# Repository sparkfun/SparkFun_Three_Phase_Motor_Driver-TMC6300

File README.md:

SparkFun 3-Phase BLDC Motor Driver - TMC6300
========================================

[*SparkFun 3-Phase BLDC Motor Driver - TMC6300 (ROB-21867)*](https://www.sparkfun.com/products/21867)

The TMC6300 from [ADI + Trinamic](https://www.trinamic.com/) is a powerful and easy to use three phase motor driver that was designed to control our [Brushless Gimbal Motor](https://www.sparkfun.com/products/20441). However, it can be used to control any 3-phase [BLDC](https://en.wikipedia.org/wiki/Brushless_DC_electric_motor "brushless DC") or [PMSM](https://en.wikipedia.org/wiki/Synchronous_motor#Permanent-magnet "permanent magnet synchronous motor") motor with up to 2A (1.4A<sub>RMS</sub>) of total drive current. Separate high-side and low-side control of the three half-bridges allows for incredible control of each phase of the [motor commutation](https://fab.cba.mit.edu/classes/865.21/topics/power_electronics/commutation/#bldc-commutation). The driver also provides temperature and short circuit protections; and a diagnostic output to indicate system faults. With a 1.8V regulated power output and an operating voltage down to 2V, the TMC6300 is suitable for low-power microcontroller and battery powered designs (min. 2 AA/NiMh cells, or 1-2 Li-Ion cells).

Our board layout has been designed with the LEDs and labels facing up, IC down. This allows the thermal pad on the board to be access if cooling is required. Additionally, the breakout pins are specially aligned to fit perfectly onto a breadboard and hold the headers more perpendicular to facilitate assembly.

Controlling 3-phase motors is not trivial and this board requires 6 PWM signals to fully control one motor. We've found the [*Arduino Simple Field Oriented Control*](https://docs.simplefoc.com/) library to work well with the board; however, there are some hadware limitations such as [supported microconrollers for `6PWM Mode`](https://docs.simplefoc.com/microcontrollers#supported-microcontrollers). With additional considerations, for integrating [position sensors](https://docs.simplefoc.com/position_sensors) into the feedback control loop.

Repository Contents
-------------------

* **[/docs](/docs/)** - Online documentation files
    * [arduino_examples](/docs/arduino_examples/) - Example code
    * [board_files](/docs/board_files/) - Files for the product design
            * [Eagle design files](/docs/board_files/eagle_files.zip) (.zip)
            * [Schematic](/docs/board_files/schematic.pdf) (.pdf)
            * [Dimensions](/docs/board_files/dimensions.pdf) (.pdf)
    * [component_documentation](/docs/component_documentation/) - Datasheets for hardware components
    * [img/hookup_guide/](/docs/img/hookup_guide/) - Images for hookup guide documentation
* **[/Hardware](/Hardware/)** - Eagle design files (.brd, .sch)

Documentation
--------------
* **[Hookup Guide (mkdocs)](http://docs.sparkfun.com/SparkFun_Three_Phase_Motor_Driver-TMC6300/)** - Hookup guide for the TMC6300 Motor Driver hosted by GitHub pages.

*Need to download or print our hookup guide?*

* [Print *(Print to PDF)* from Single-Page View](http://docs.sparkfun.com/SparkFun_Three_Phase_Motor_Driver-TMC6300/single_page)
* [Download PDF](http://docs.sparkfun.com/SparkFun_Three_Phase_Motor_Driver-TMC6300/board_files/hookup_guide.pdf) *(Beta - Mostly works, but some attributes may be broken.)*

Product Variants
----------------
* [ROB-21867](https://www.sparkfun.com/products/21867)- v1.0, Initial Release

Version History
---------------
* [v01](https://github.com/sparkfun/SparkFun_Three_Phase_Motor_Driver-TMC6300/releases/tag/v10) - Initial Release

License Information
-------------------

This product is _**open source**_! 

Please review the LICENSE.md file for license information. 

If you have any questions or concerns about licensing, please contact technical support on our [SparkFun forums](https://forum.sparkfun.com/viewforum.php?f=152).

Distributed as-is; no warranty is given.

- Your friends at SparkFun.

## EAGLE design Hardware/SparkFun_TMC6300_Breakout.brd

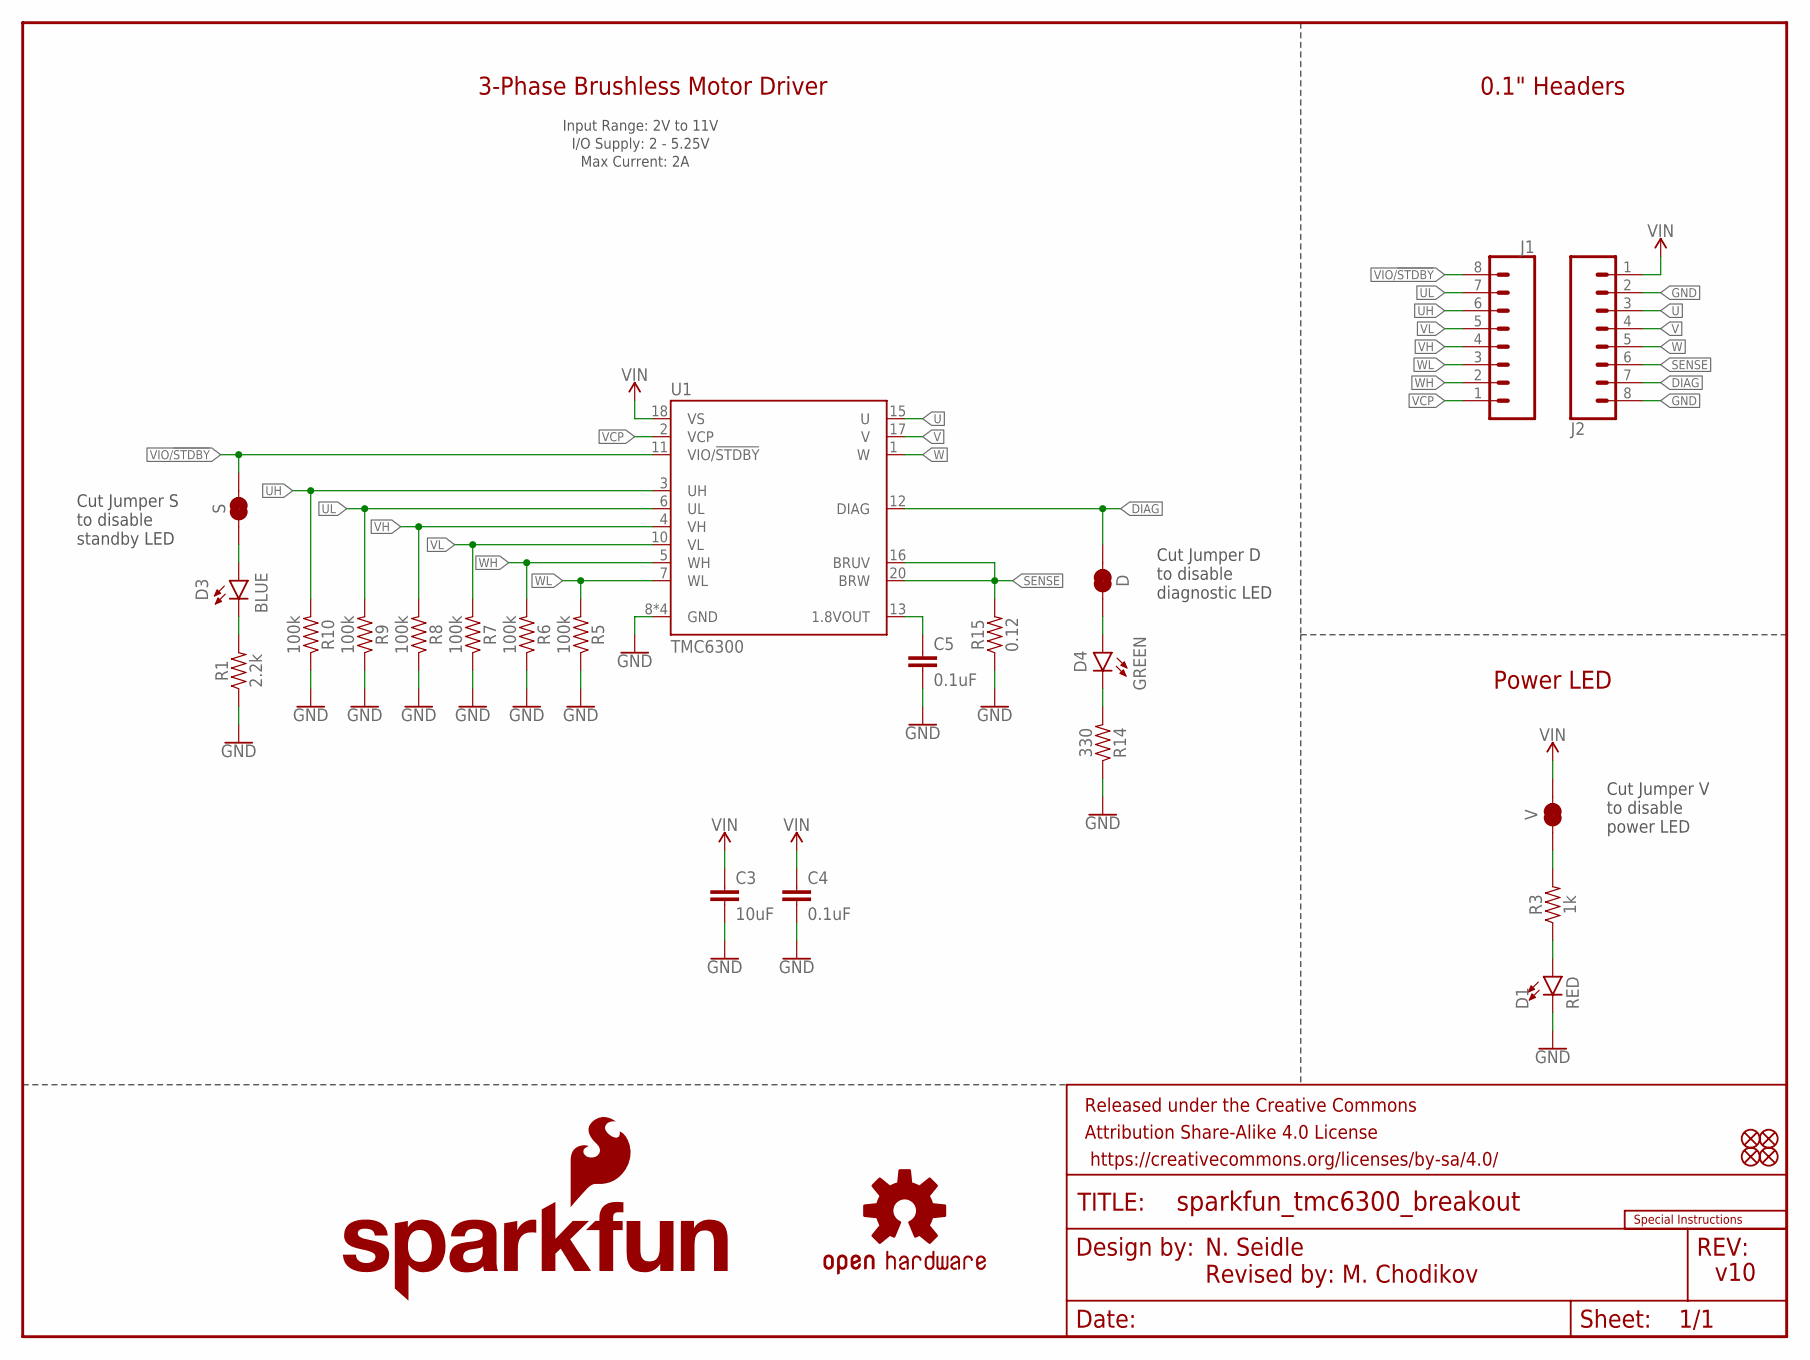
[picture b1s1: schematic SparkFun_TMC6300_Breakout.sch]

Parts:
C3: 10uF; 0805
C4, C5: 0.1uF; 0603
D: JUMPER-SMT_2_NC_TRACE_SILK; SMT-JUMPER_2_NC_TRACE_SILK
D1: RED; LED-0603
D3: BLUE; LED-0603
D4: GREEN; LED-0603
FD1, FD2, FD3, FD4: FIDUCIALUFIDUCIAL; FIDUCIAL-MICRO
FRAME1: FRAME-LETTER; CREATIVE_COMMONS
J1, J2: CONN_08LOCK_NO_SILK; 1X08_LOCK_NO_SILK
LOGO2: SPECIAL_INSTRUCTIONS-ORDERING; ORDERING_INSTRUCTIONS
LOGO3: SFE_LOGO_NAME.08_INCH; SFE_LOGO_NAME_.08
LOGO4: SFE_LOGO_FLAME.1_INCH; SFE_LOGO_FLAME_.1
LOGO5: OSHW-LOGOS; OSHW-LOGO-S
R1: 2.2k; 0603
R3: 1k; 0603
R5, R6, R7, R8, R9, R10: 100k; 0603
R14: 330; 0603
R15: 0.12; 1206
S: JUMPER-SMT_2_NC_TRACE_SILK; SMT-JUMPER_2_NC_TRACE_SILK
U1: TMC6300; QFN-20
V: JUMPER-SMT_2_NC_TRACE_SILK; SMT-JUMPER_2_NC_TRACE_SILK

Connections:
DIAG: D.2, J2.7, U1.12 (DIAG)
GND: C3.2, C4.2, C5.2, D1.C, J2.2, J2.8, R1.1, R5.1, R6.1, R7.1, R8.1, R9.1, R10.1, R14.1, R15.1, U1.8 (GND), U1.9 (GND), U1.14 (GND), U1.PAD (GND)
unnamed: R3.2, V.1
unnamed: D1.A, R3.1
unnamed: D3.A, S.1
unnamed: C5.1, U1.13 (1.8VOUT)
unnamed: D.1, D4.A
unnamed: D3.C, R1.2
unnamed: D4.C, R14.2
SENSE: J2.6, R15.2, U1.16 (BRUV), U1.20 (BRW)
U: J2.3, U1.15 (U)
UH: J1.6, R10.2, U1.3 (UH)
UL: J1.7, R9.2, U1.6 (UL)
V: J2.4, U1.17 (V)
VCP: J1.1, U1.2 (VCP)
VH: J1.4, R8.2, U1.4 (VH)
VIN: C3.1, C4.1, J2.1, U1.18 (VS), V.2
VIO/!STDBY!: J1.8, S.2, U1.11 (VIO/!STDBY!)
VL: J1.5, R7.2, U1.10 (VL)
W: J2.5, U1.1 (W)
WH: J1.2, R6.2, U1.5 (WH)
WL: J1.3, R5.2, U1.7 (WL)

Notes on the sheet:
0.1" Headers
Power LED
I/O Supply: 2 - 5.25V
3-Phase Brushless Motor Driver
N. Seidle
v10
Revised by: M. Chodikov
Input Range: 2V to 11V
Max Current: 2A
Cut Jumper S to disable standby LED
Cut Jumper D to disable diagnostic LED
Cut Jumper V to disable power LED

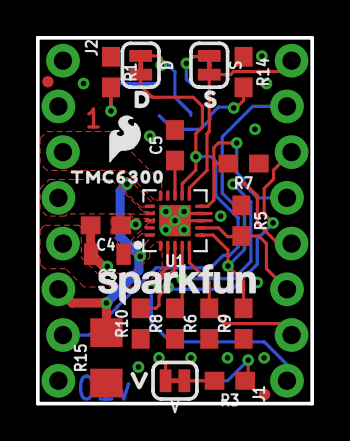
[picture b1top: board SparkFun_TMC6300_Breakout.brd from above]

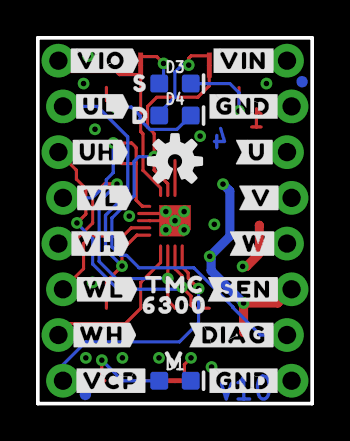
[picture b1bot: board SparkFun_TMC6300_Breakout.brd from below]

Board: 4 copper layers, 15.2 x 20.3 mm, 56 parts (27 on the bottom side), 22 nets.

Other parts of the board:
U$1, U$28: #GND#1
U$2: #SEN#0
U$3: #DIAG#0
U$4: TMC630063003454
U$9: #U#6
U$12: #VCP#0
U$13: #VIO#1
U$15: 63001
U$16, U$18: D0
U$19, U$27: S1
U$20, U$26: V2
U$21: #UH#5
U$22: #UL#4
U$23: TMC0
U$24: #VIN#0
U$25: #V#7
U$30: #VH#2
U$31: #VL#3
U$32: #W#8
U$33: #WH#1
U$34: #WL#0

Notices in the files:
parts and their libraries:
SparkFun-Capacitors: Licensing: Creative Commons ShareAlike 4.0 International - https://creativecommons.org/licenses/by-sa/4.0
SparkFun-Aesthetics: Released under the Creative Commons Attribution Share-Alike 4.0 License
SparkFun-Aesthetics: https://creativecommons.org/licenses/by-sa/4.0
